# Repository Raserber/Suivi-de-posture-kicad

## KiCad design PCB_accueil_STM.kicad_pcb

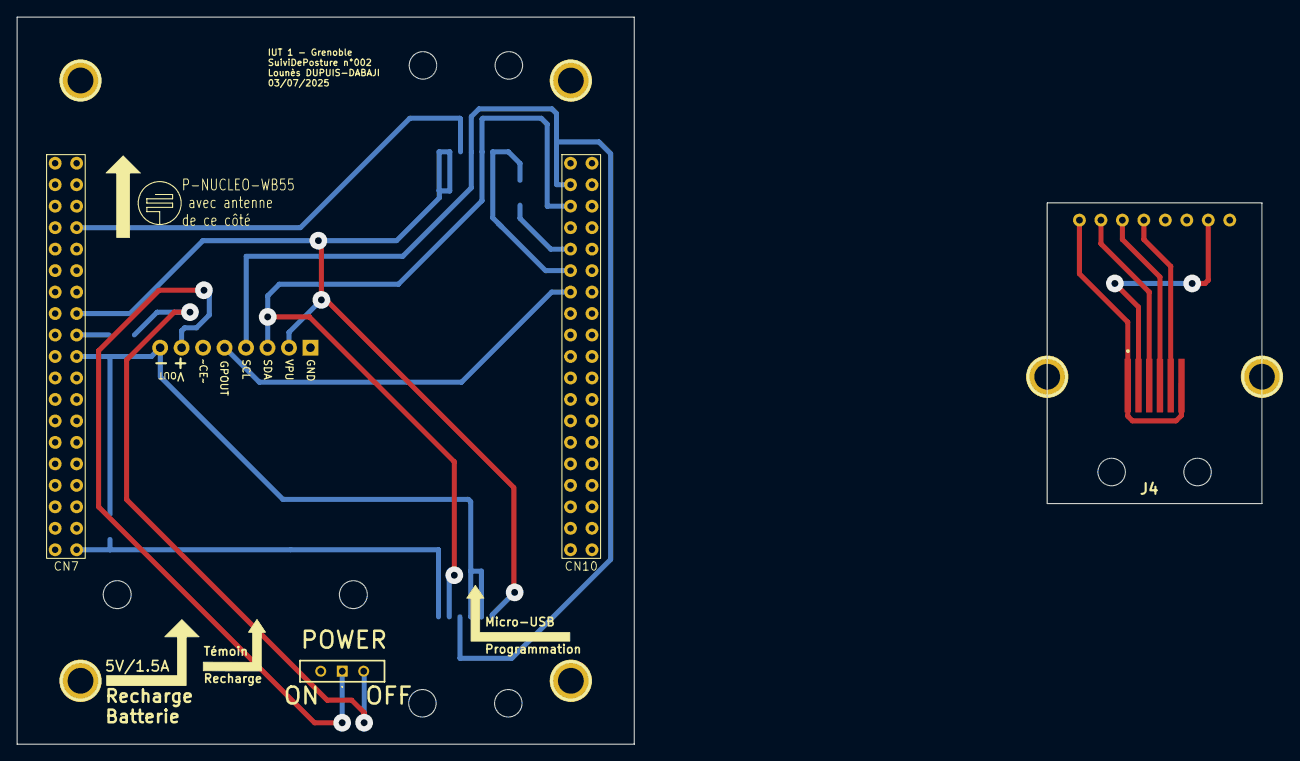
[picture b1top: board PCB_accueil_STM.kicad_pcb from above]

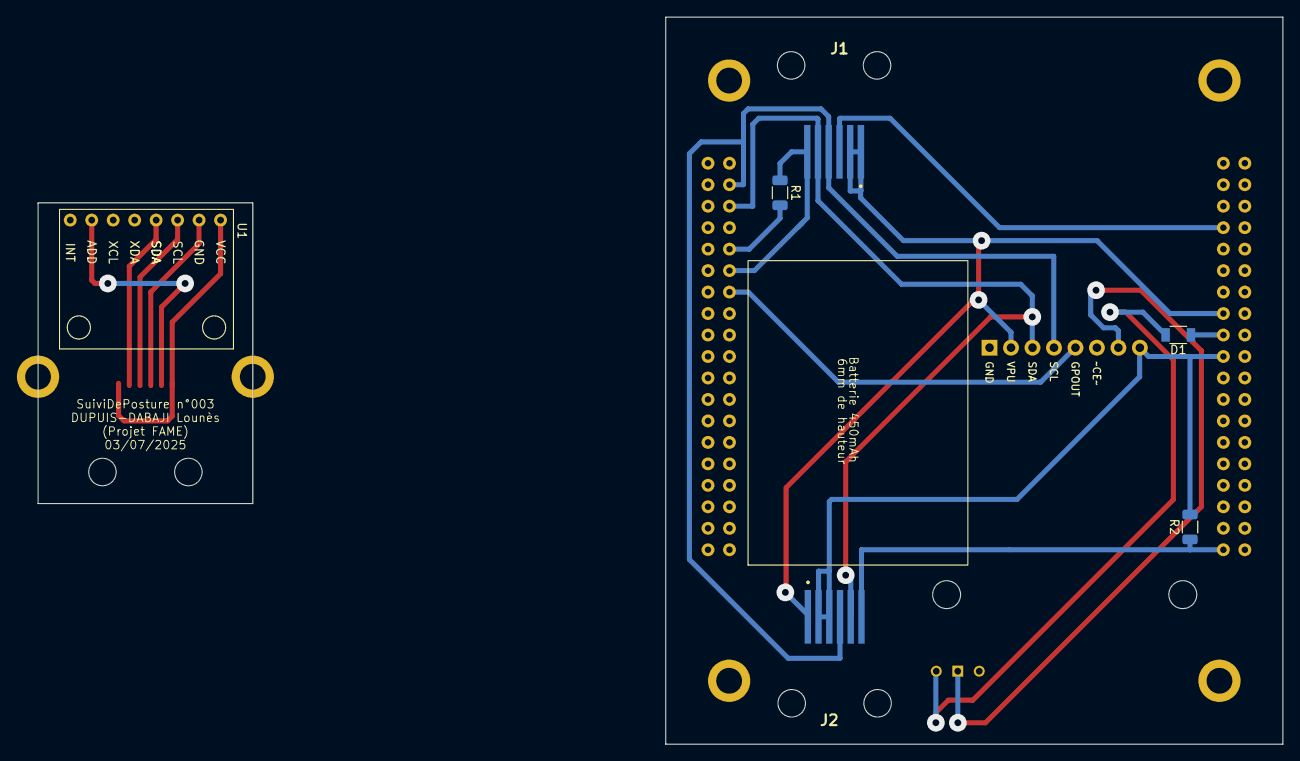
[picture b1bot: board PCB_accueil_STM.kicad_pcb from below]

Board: 2 copper layers, 147.2 x 86.0 mm, 17 parts (6 on the bottom side), 17 nets.

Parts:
1PIN, 1PIN#2, 1PIN#3, 1PIN#4, 1PIN#5, 1PIN#6: P***; IUT_TrouFixation
CN7: Nucleo_STM32WB_CN7
CN10: Nucleo_STM32WB_CN10
D1: D; IUT_Capa_CMS_1206
J1: RJ12 Haut; 95501-6669
J2: RJ12 Bas; 95501-6669
J3: SparkFun Battery Babysitter; babybattery
J4: RJ12 capteur; 95501-6669
R1, R2: 10k; C_1206_3216Metric
S1: Switch; SIP
U1: module_mpu6050

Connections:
+3V3: CN7.16 (3V3), J1.1, J1.2, J2.1, J3.2
/I2C_SCL: CN10.3 (I2C1_SCL/PB8), J1.4, J2.4, J3.4
/I2C_SDA: CN10.5 (I2C1_SDA/PB9), J1.5, J2.5, J3.3
/INT_LOW_BAT: CN10.13 (PA6), J3.5
/temoin_connexion_bas: CN7.38 (PC2), J2.6, R2.1
/temoin_connexion_haut: CN10.11 (PA5), J1.6, R1.1
GND: CN7.8 (GND), J1.3
GND2: CN7.20 (GND), J2.2, J2.3, J3.8, R2.2
GND3: CN10.9 (GND), R1.2
unnamed: D1.2 (A), S1.2 (NO)
unnamed: J3.7, S1.1 (COM)
unnamed: J4.2, U1.7 (ADD)
unnamed: J4.3, U1.2 (GND)
unnamed: J4.4, U1.3 (SCL)
unnamed: J4.5, U1.4 (SDA)
unnamed: J4.1, J4.6, U1.1 (VCC)
VBAT: CN7.18 (5V), D1.1 (K)

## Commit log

2025-08-21 rentrée scolaire
